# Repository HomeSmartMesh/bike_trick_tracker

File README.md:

# bike_trick_tracker
Tracking sensors for bike movements like height from pressure 9 axis and ToF with record and telemetry

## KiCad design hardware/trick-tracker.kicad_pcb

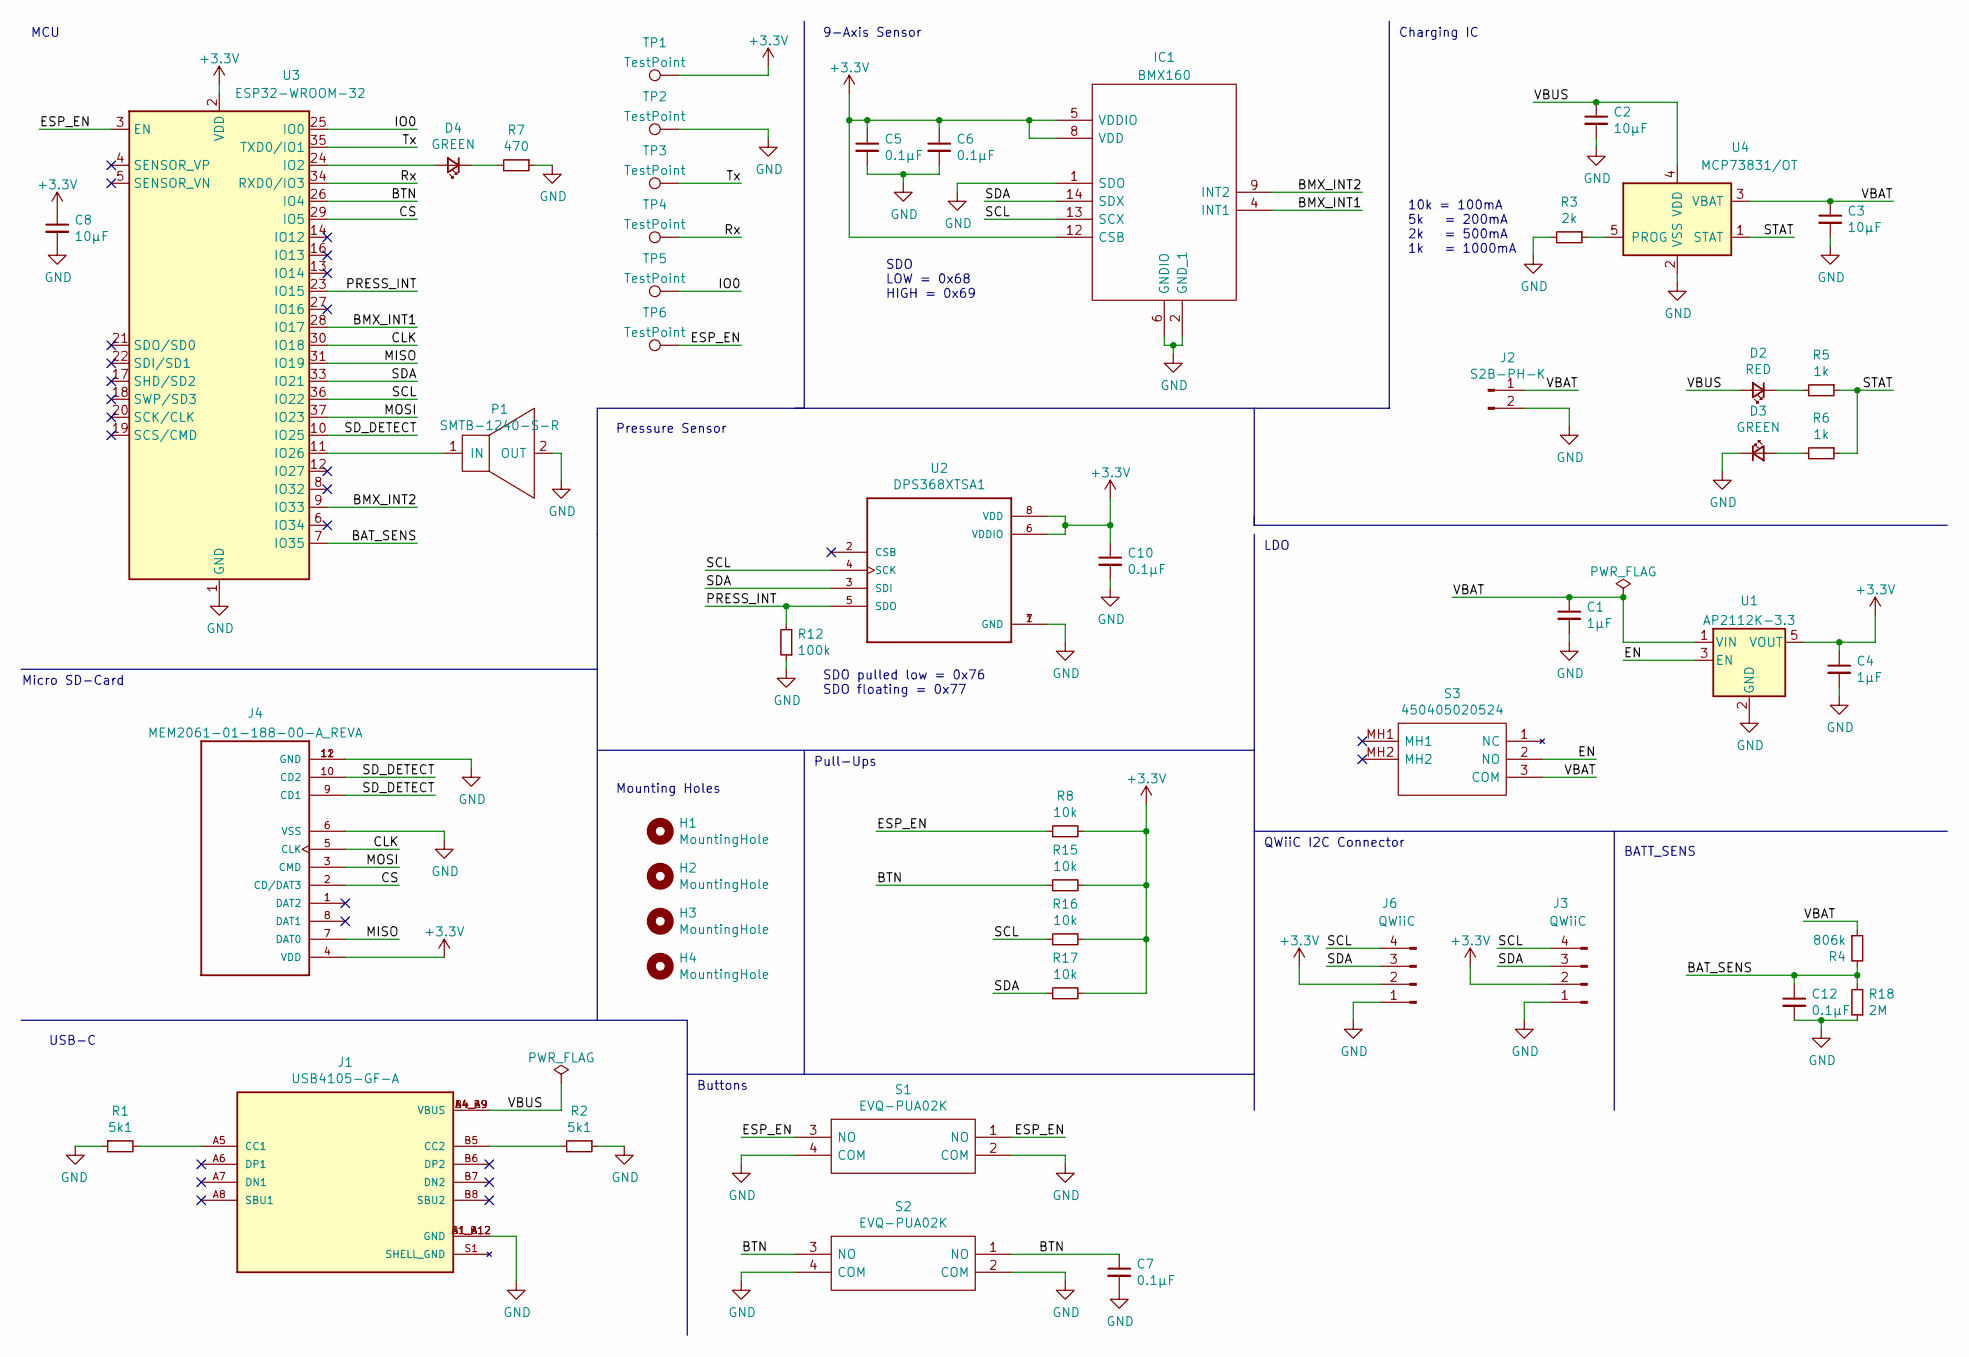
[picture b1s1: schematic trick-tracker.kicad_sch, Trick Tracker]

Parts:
C1, C4: 1µF; C_0603_1608Metric
C2, C3, C8: 10µF; C_0603_1608Metric
C5, C6, C7, C10, C12: 0.1µF; C_0603_1608Metric
D2: RED; LED_0603_1608Metric
D3, D4: GREEN; LED_0603_1608Metric
H1, H2, H3, H4: MountingHole; MountingHole_2.5mm_Pad_Via
IC1: BMX160; PQFN50P300X250X88-14N; Manufacturer_Part_Number BMX160; Mouser Part Number 262-BMX160
J1: USB4105-GF-A; GCT_USB4105-GF-A
J2: S2B-PH-K; JST_PH_S2B-PH-SM4-TB_1x02-1MP_P2.00mm_Horizontal
J3, J6: QWiiC; JST_SH_SM04B-SRSS-TB_1x04-1MP_P1.00mm_Horizontal
J4: MEM2061-01-188-00-A_REVA; GCT_MEM2061-01-188-00-A_REVA
P1: SMTB-1240-S-R
R1, R2: 5k1; R_0603_1608Metric
R3: 2k; R_0603_1608Metric
R4: 806k; R_0603_1608Metric
R5, R6: 1k; R_0603_1608Metric
R7: 470; R_0603_1608Metric
R8, R15, R16, R17: 10k; R_0603_1608Metric
R12: 100k; R_0603_1608Metric
R18: 2M; R_0603_1608Metric
S1, S2: EVQ-PUA02K; EVQPUA02K
S3: 450405020524
TP1, TP2, TP3, TP4, TP5, TP6: TestPoint; TestPoint_Pad_D1.5mm
U1: AP2112K-3.3; SOT-23-5
U2: DPS368XTSA1; XDCR_DPS368XTSA1
U3: ESP32-WROOM-32
U4: MCP73831/OT; SOT-23-5

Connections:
+3V3: C4.1, C5.1, C6.1, C8.1, C10.1, IC1.5 (VDDIO), IC1.8 (VDD), IC1.12 (CSB), J3.2, J4.4 (VDD), J6.2, R8.2, R15.2, R16.2, R17.2, TP1.1, U1.5 (VOUT), U2.6 (VDDIO), U2.8 (VDD), U3.2 (VDD)
/BAT_SENS: C12.1, R4.2, R18.2, U3.7 (IO35)
/BMX_INT1: IC1.4 (INT1), U3.28 (IO17)
/BMX_INT2: IC1.9 (INT2), U3.9 (IO33)
/BTN: C7.1, R15.1, S2.1 (NO), S2.3 (NO), U3.26 (IO4)
/CLK: J4.5 (CLK), U3.30 (IO18)
/CS: J4.2 (CD/DAT3), U3.29 (IO5)
/EN: S3.2 (NO), U1.3 (EN)
/ESP_EN: R8.1, S1.1 (NO), S1.3 (NO), TP6.1, U3.3 (EN)
/IO0: TP5.1, U3.25 (IO0)
/MISO: J4.7 (DAT0), U3.31 (IO19)
/MOSI: J4.3 (CMD), U3.37 (IO23)
/PRESS_INT: R12.2, U2.5 (SDO), U3.23 (IO15)
/Rx: TP4.1, U3.34 (RXD0/IO3)
/SCL: IC1.13 (SCX), J3.4, J6.4, R16.1, U2.4 (SCK), U3.36 (IO22)
/SDA: IC1.14 (SDX), J3.3, J6.3, R17.1, U2.3 (SDI), U3.33 (IO21)
/SD_DETECT: J4.9 (CD1), J4.10 (CD2), U3.10 (IO25)
/STAT: R5.1, R6.1, U4.1 (STAT)
/Tx: TP3.1, U3.35 (TXD0/IO1)
/VBAT: C1.1, C3.1, J2.1, R4.1, S3.3 (COM), U1.1 (VIN), U4.3 (VBAT)
/VBUS: C2.1, D2.2 (A), J1.A4_B9 (VBUS), J1.B4_A9 (VBUS), U4.4 (VDD)
GND: C1.2, C2.2, C3.2, C4.2, C5.2, C6.2, C7.2, C8.2, C10.2, C12.2, D3.1 (K), IC1.1 (SDO), IC1.2 (GND_1), IC1.3 (GND_2), IC1.6 (GNDIO), IC1.7 (GND_3), J1.A1_B12 (GND), J1.B1_A12 (GND), J2.2, J3.1, J4.6 (VSS), J4.11 (GND), J4.12 (GND), J6.1, P1.2 (OUT), R1.1, R2.1, R3.2, R7.1, R12.1, R18.1, S1.2 (COM), S1.4 (COM), S2.2 (COM), S2.4 (COM), TP2.1, U1.2 (GND), U2.1 (GND), U2.7 (GND), U3.1 (GND), U3.15 (GND), U3.38 (GND), U3.39 (GND), U4.2 (VSS)
unnamed: D2.1 (K), R5.2
unnamed: D3.2 (A), R6.2
unnamed: D4.1 (K), R7.2
unnamed: D4.2 (A), U3.24 (IO2)
unnamed: J1.A5 (CC1), R1.2
unnamed: J1.B5 (CC2), R2.2
unnamed: P1.1 (IN), U3.11 (IO26)
unnamed: R3.1, U4.5 (PROG)

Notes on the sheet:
Charging IC
10k = 100mA 5k = 200mA 2k = 500mA 1k = 1000mA
SDO LOW = 0x68 HIGH = 0x69
Mounting Holes
Pull-Ups
QWiiC I2C Connector
9-Axis Sensor
SDO pulled low = 0x76 SDO floating = 0x77
MCU
LDO
Micro SD-Card
BATT_SENS
USB-C
Buttons
Pressure Sensor

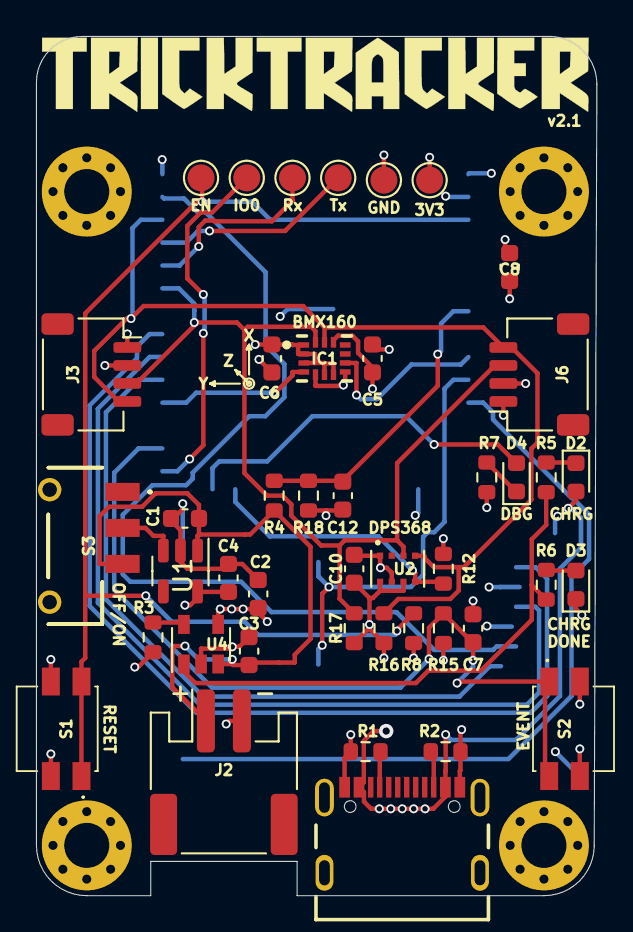
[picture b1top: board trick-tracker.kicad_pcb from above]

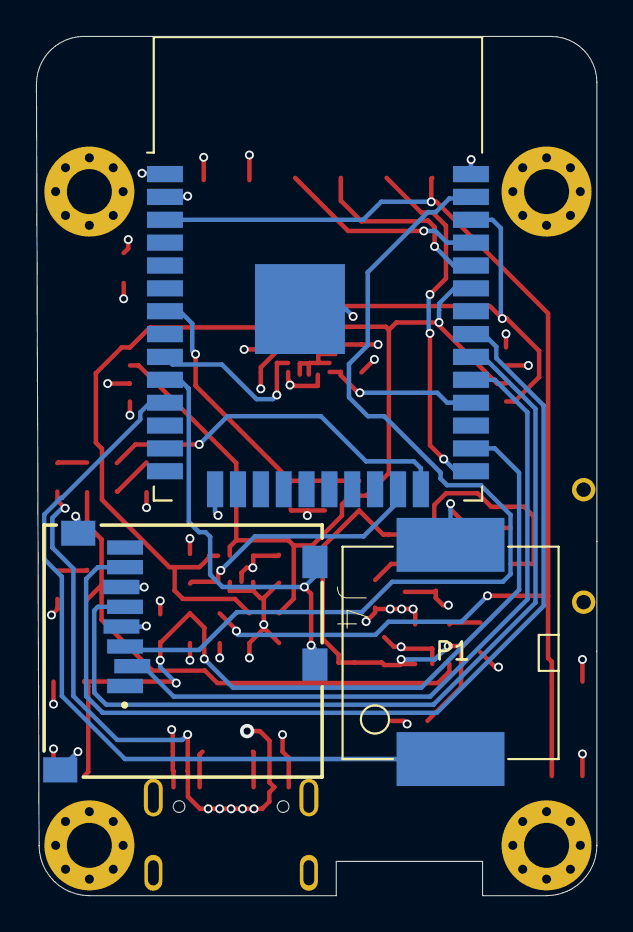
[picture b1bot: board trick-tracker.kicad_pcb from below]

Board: 4 copper layers, 31.1 x 47.7 mm, 50 parts (3 on the bottom side), 30 nets.

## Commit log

2021-05-23 Add schematics and layout
2021-05-23 Add Micro SD-Card holder
2021-05-23 Moved components
2021-05-23 Changed LED resistor value to 1k
2021-05-23 Add Labels to schematic
2021-05-24 Exchanged battery connector with SMD version
2021-05-24 Add BMX055 sensor component
2021-05-24 Fix BAT_SENS and added it to an ADC - exchanged with an interrupt
2021-05-24 Add ESD protection for USB
2021-05-24 Exchanged SD Card holder with one which can be hand-soldered
2021-05-25 Started layouting
2021-05-26 Finished trace routing
2021-05-26 Placed and moved labels
2021-05-28 Small adjustments + rounded corners + BOM HTML
2021-06-01 Add connector (placeholder) + extra GND TP
2021-06-01 Start layout BN055 sensor to replace the other accel sensor
2021-06-01 Add and layed out BMX160 Sensor
2021-06-02 Added Labels
2021-06-04 Removed unused connector
2021-06-05 Made some small adjustments
2021-06-05 Generated Gerbers and BOM
2021-10-01 Add Gerbers
2021-10-03 Plott schematics
2022-02-19 Changed Layout to use ESP32 instead of nRF52
2022-04-12 Replaced nRF52 with ESP32
2022-08-19 current changed (to be checked again)
2022-08-20 add testpoints + test programms
2022-11-06 gernerated bom
2022-11-06 Refactor Test code
2022-11-06 Changed schematics and layout to fit current changes
2022-11-06 Toit test code
2022-11-06 Generated bom
2022-11-30 Added a housing created with FreeCAD 0.20
2022-11-30 Added toit firmware for data tracking to collect first data
    Tracking software to track sensor data and timestamp into CSV file on the SD-Card
2023-04-13 Add files for the case
    NOTE: the case is fine but it does not fit perfectly! It needs a little adjustments, everything is super tight
2023-04-13 Tiny changes to the layout
2023-04-13 Added some testing code for micropython and arduino code
